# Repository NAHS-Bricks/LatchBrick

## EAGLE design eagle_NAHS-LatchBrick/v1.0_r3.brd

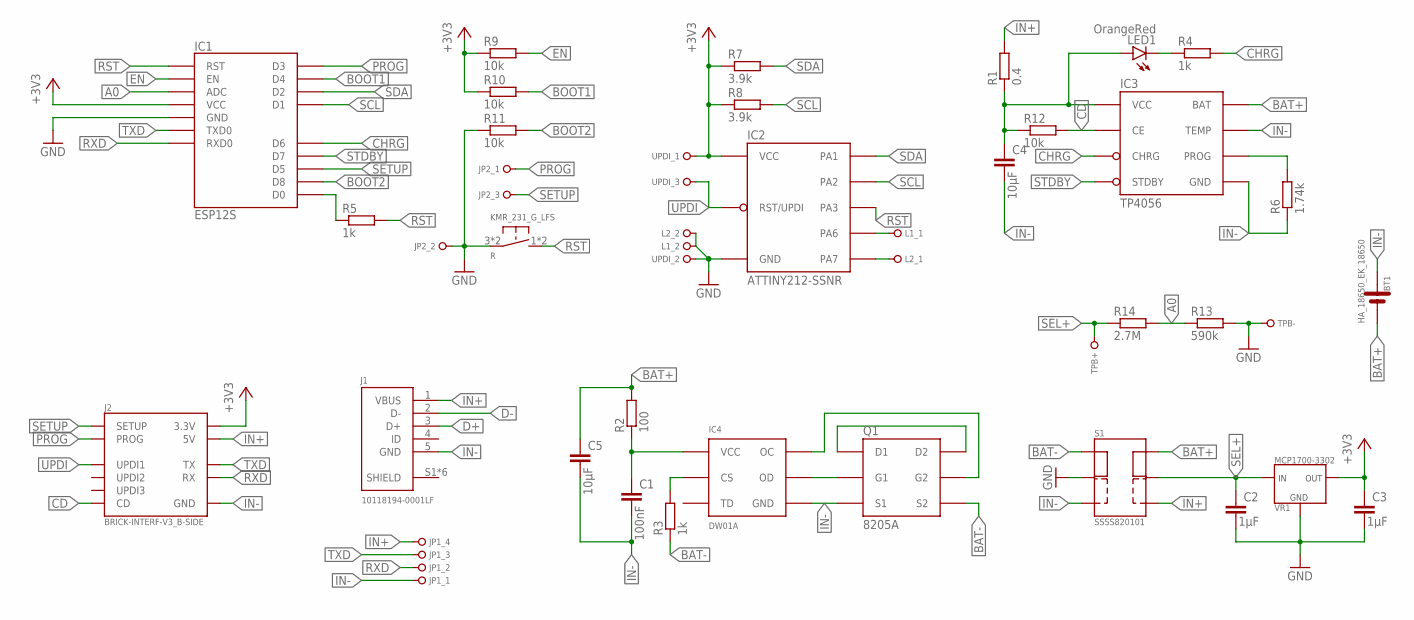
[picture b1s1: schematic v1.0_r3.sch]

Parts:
BT1: HA_18650_EK_18650
C1: 100nF; C0805
C2, C3: 1µF; C0805
C4, C5: 10µF; C0805
IC1: ESP12S
IC2: ATTINY212-SSNR; SOIC8
IC3: TP4056; SO8-THERMALPAD
IC4: DW01A; SOT23-6
J1: 10118194-0001LF
J2: BRICK-INTERF-V3_B-SIDE; DF9-11P-1V(32)
JP1: PINHD_1X04_R_1; 1X04_R_1
JP2: PINHD_1X03_R_1; 1X03_R_1
L1, L2: PINHD_1X02_R_1; 1X02_R_1
LED1: OrangeRed; CHIP-LED0805
Q1: 8205A; TSSOP8
R: KMR_231_G_LFS
R1: 0.4; R0805
R2: 100; R0805
R3, R4, R5: 1k; R0805
R6: 1.74k; R0805
R7, R8: 3.9k; R0805
R9, R10, R11, R12: 10k; R0805
R13: 590k; R0805
R14: 2.7M; R0805
S1: SSSS820101
TPB+: PINHD_1X01_S_0.8; 1X01_S_0.8
TPB-: PINHD_1X01_S_0.8; 1X01_S_0.8
UPDI: PINHD_1X03_R_1; 1X03_R_1
VR1: MCP1700-3302; SOT23

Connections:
+3V3: C3.1, IC1.VCC, IC2.1 (VCC), J2.10 (3.3V), R7.1, R8.1, R9.1, R10.1, UPDI.1, VR1.2 (OUT)
A0: IC1.ADC, R13.1, R14.2
BAT+: BT1.P1 (PLUS), BT1.P2 (PLUS), BT1.P3 (PLUS), C5.1, IC3.5 (BAT), R2.2, S1.6
BAT-: Q1.6 (S2), Q1.7 (S2), R3.1, S1.3
BOOT1: IC1.GPIO2 (D4), R10.2
BOOT2: IC1.GPIO15 (D8), R11.2
CD: IC3.8 (CE), J2.5 (CD), R12.2
CHRG: IC1.GPIO12 (D6), IC3.7 (CHRG), R4.2
D+: J1.3 (D+)
D-: J1.2 (D-)
EN: IC1.EN, R9.2
GND: C2.2, C3.2, IC1.GND, IC2.8 (GND), JP2.2, L1.2, L2.2, R.3 (2), R.4 (2), R11.1, R13.2, S1.2, TPB-.1, UPDI.2, VR1.1 (GND)
IN+: J1.1 (VBUS), J2.4 (5V), JP1.4, R1.2, S1.4
IN-: BT1.M1 (MINUS), BT1.M2 (MINUS), BT1.M3 (MINUS), C1.2, C4.2, C5.2, IC3.1 (TEMP), IC3.3 (GND), IC3.T1 (GND), IC3.T2 (GND), IC3.T3 (GND), IC3.T4 (GND), IC3.T5 (GND), IC3.T6 (GND), IC3.T7 (GND), IC3.T8 (GND), IC4.6 (GND), J1.5 (GND), J2.6 (GND), JP1.1, Q1.2 (S1), Q1.3 (S1), R6.1, S1.1
unnamed: C4.1, IC3.4 (VCC), LED1.A, R1.1, R12.1
unnamed: IC3.2 (PROG), R6.2
unnamed: IC4.2 (CS), R3.2
unnamed: C1.1, IC4.5 (VCC), R2.1
unnamed: IC2.3 (PA7), L2.1
unnamed: IC2.2 (PA6), L1.1
unnamed: LED1.C, R4.1
unnamed: IC4.1 (OD), Q1.4 (G1)
unnamed: Q1.1 (D1), Q1.8 (D2)
unnamed: IC4.3 (OC), Q1.5 (G2)
PROG: IC1.GPIO0 (D3), J2.3 (PROG), JP2.1
RST: IC1.RST, IC2.7 (PA3), R.1, R.2 (1), R5.2
RXD: IC1.RXD0, J2.11 (RX), JP1.2
SCL: IC1.GPIO5 (D1), IC2.5 (PA2), R8.2
SDA: IC1.GPIO4 (D2), IC2.4 (PA1), R7.2
SEL+: C2.1, R14.1, S1.5, TPB+.1, VR1.3 (IN)
SETUP: IC1.GPIO14 (D5), J2.2 (SETUP), JP2.3
SHIELD: J1.S1 (SHIELD), J1.S2 (SHIELD), J1.S3 (SHIELD), J1.S4 (SHIELD), J1.S5 (SHIELD), J1.S6 (SHIELD)
STDBY: IC1.GPIO13 (D7), IC3.6 (STDBY)
TXD: IC1.TXD0, J2.1 (TX), JP1.3
UPDI: IC2.6 (RST/UPDI), J2.7 (UPDI1), UPDI.3
WAKE: IC1.GPIO16 (D0), R5.1

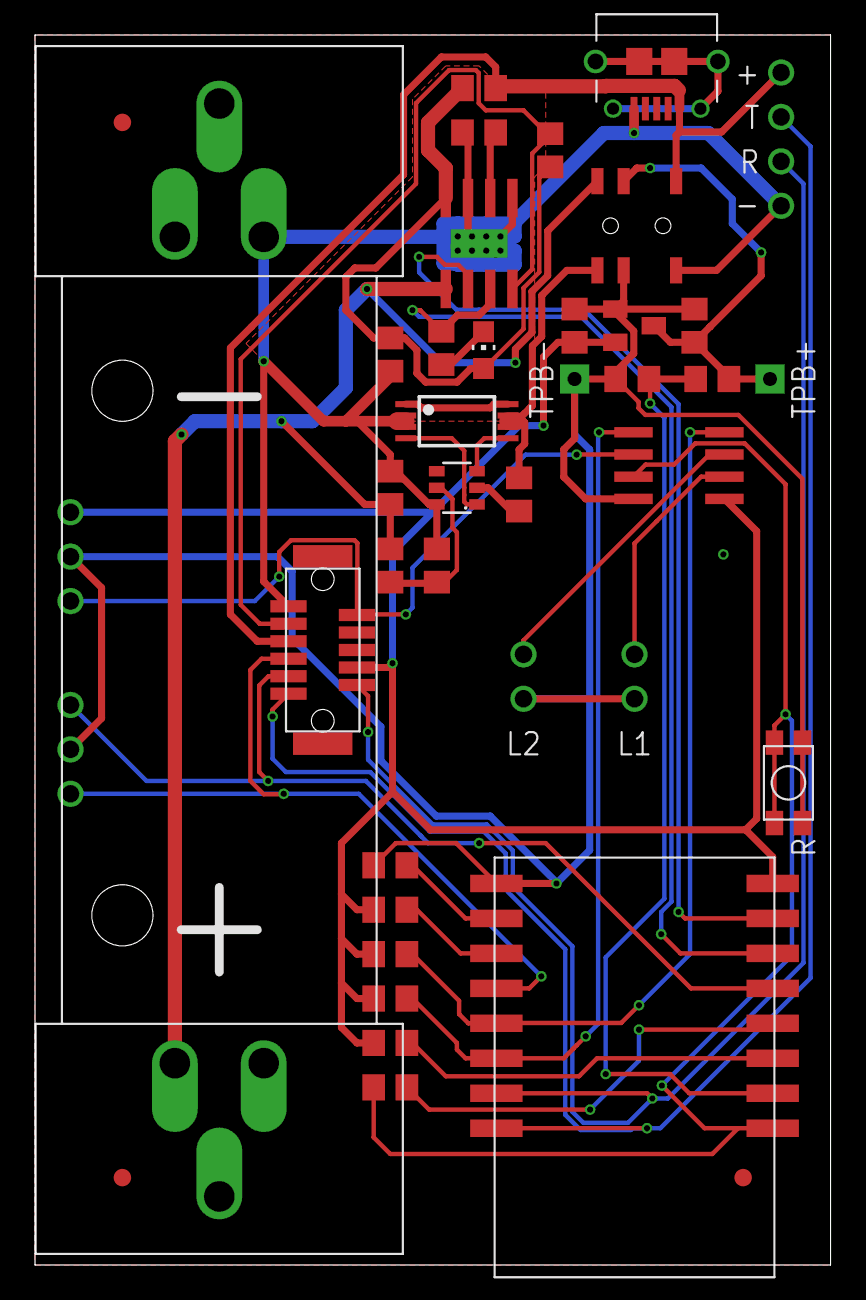
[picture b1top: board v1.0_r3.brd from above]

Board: 2 copper layers, 45.5 x 70.3 mm, 41 parts (0 on the bottom side), 34 nets.

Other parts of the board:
FD1, FD2, FD3: FIDUCIAL

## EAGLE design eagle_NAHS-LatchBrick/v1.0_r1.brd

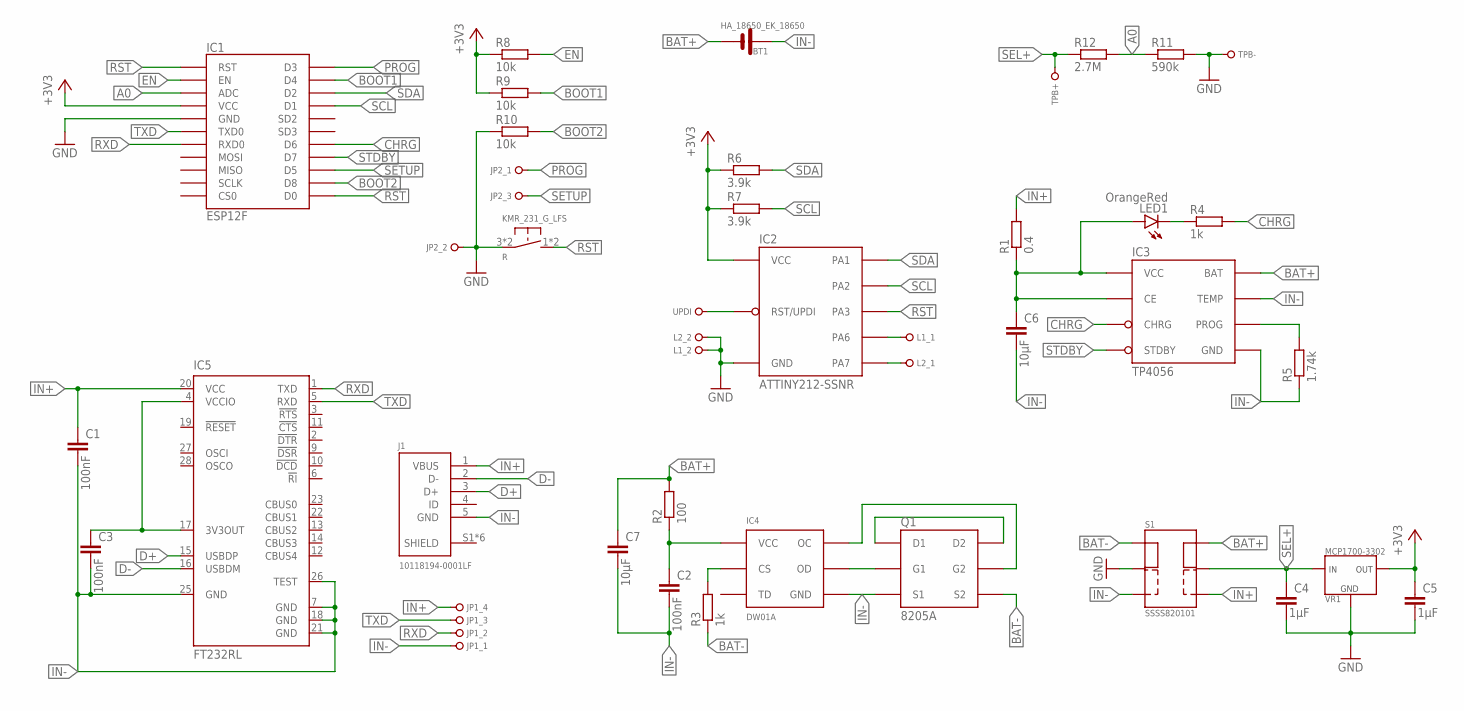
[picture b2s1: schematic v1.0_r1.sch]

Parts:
BT1: HA_18650_EK_18650
C1, C2, C3: 100nF; C0805
C4, C5: 1µF; C0805
C6, C7: 10µF; C0805
IC1: ESP12F; ESP12
IC2: ATTINY212-SSNR; SOIC8
IC3: TP4056; SO8-THERMALPAD
IC4: DW01A; SOT23-6
IC5: FT232RL; SSOP28
J1: 10118194-0001LF
JP1: PINHD_1X04_R_1; 1X04_R_1
JP2: PINHD_1X03_R_1; 1X03_R_1
L1, L2: PINHD_1X02_R_1; 1X02_R_1
LED1: OrangeRed; CHIP-LED0805
Q1: 8205A; TSSOP8
R: KMR_231_G_LFS
R1: 0.4; R0805
R2: 100; R0805
R3, R4: 1k; R0805
R5: 1.74k; R0805
R6, R7: 3.9k; R0805
R8, R9, R10: 10k; R0805
R11: 590k; R0805
R12: 2.7M; R0805
S1: SSSS820101
TPB+: PINHD_1X01_S_0.8; 1X01_S_0.8
TPB-: PINHD_1X01_S_0.8; 1X01_S_0.8
UPDI: PINHD_1X01_S_0.8; 1X01_S_0.8
VR1: MCP1700-3302; SOT23

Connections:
+3V3: C5.1, IC1.VCC, IC2.1 (VCC), R6.1, R7.1, R8.1, R9.1, VR1.2 (OUT)
A0: IC1.ADC, R11.1, R12.2
BAT+: BT1.P1 (PLUS), BT1.P2 (PLUS), BT1.P3 (PLUS), C7.1, IC3.5 (BAT), R2.2, S1.6
BAT-: Q1.6 (S2), Q1.7 (S2), R3.1, S1.3
BOOT1: IC1.GPIO2 (D4), R9.2
BOOT2: IC1.GPIO15 (D8), R10.2
CHRG: IC1.GPIO12 (D6), IC3.7 (CHRG), R4.2
D+: IC5.15 (USBDP), J1.3 (D+)
D-: IC5.16 (USBDM), J1.2 (D-)
EN: IC1.EN, R8.2
GND: C4.2, C5.2, IC1.GND, IC2.8 (GND), JP2.2, L1.2, L2.2, R.3 (2), R.4 (2), R10.1, R11.2, S1.2, TPB-.1, VR1.1 (GND)
IN+: C1.1, IC5.20 (VCC), J1.1 (VBUS), JP1.4, R1.2, S1.4
IN-: BT1.M1 (MINUS), BT1.M2 (MINUS), BT1.M3 (MINUS), C1.2, C2.2, C3.2, C6.2, C7.2, IC3.1 (TEMP), IC3.3 (GND), IC3.T1 (GND), IC3.T2 (GND), IC3.T3 (GND), IC3.T4 (GND), IC3.T5 (GND), IC3.T6 (GND), IC3.T7 (GND), IC3.T8 (GND), IC4.6 (GND), IC5.7 (GND), IC5.18 (GND), IC5.21 (GND), IC5.25 (GND), IC5.26 (TEST), J1.5 (GND), JP1.1, Q1.2 (S1), Q1.3 (S1), R5.1, S1.1
L1: IC2.2 (PA6), L1.1
L2: IC2.3 (PA7), L2.1
unnamed: C6.1, IC3.4 (VCC), IC3.8 (CE), LED1.A, R1.1
unnamed: IC3.2 (PROG), R5.2
unnamed: IC4.2 (CS), R3.2
unnamed: C2.1, IC4.5 (VCC), R2.1
unnamed: LED1.C, R4.1
unnamed: IC4.1 (OD), Q1.4 (G1)
unnamed: Q1.1 (D1), Q1.8 (D2)
unnamed: IC4.3 (OC), Q1.5 (G2)
PROG: IC1.GPIO0 (D3), JP2.1
RST: IC1.GPIO16 (D0), IC1.RST, IC2.7 (PA3), R.1, R.2 (1)
RXD: IC1.RXD0, IC5.1 (TXD), JP1.2
SCL: IC1.GPIO5 (D1), IC2.5 (PA2), R7.2
SDA: IC1.GPIO4 (D2), IC2.4 (PA1), R6.2
SEL+: C4.1, R12.1, S1.5, TPB+.1, VR1.3 (IN)
SETUP: IC1.GPIO14 (D5), JP2.3
SHIELD: J1.S1 (SHIELD), J1.S2 (SHIELD), J1.S3 (SHIELD), J1.S4 (SHIELD), J1.S5 (SHIELD), J1.S6 (SHIELD)
STDBY: IC1.GPIO13 (D7), IC3.6 (STDBY)
TXD: IC1.TXD0, IC5.5 (RXD), JP1.3
UPDI: IC2.6 (RST/UPDI), UPDI.1
VCCIO: C3.1, IC5.4 (VCCIO), IC5.17 (3V3OUT)

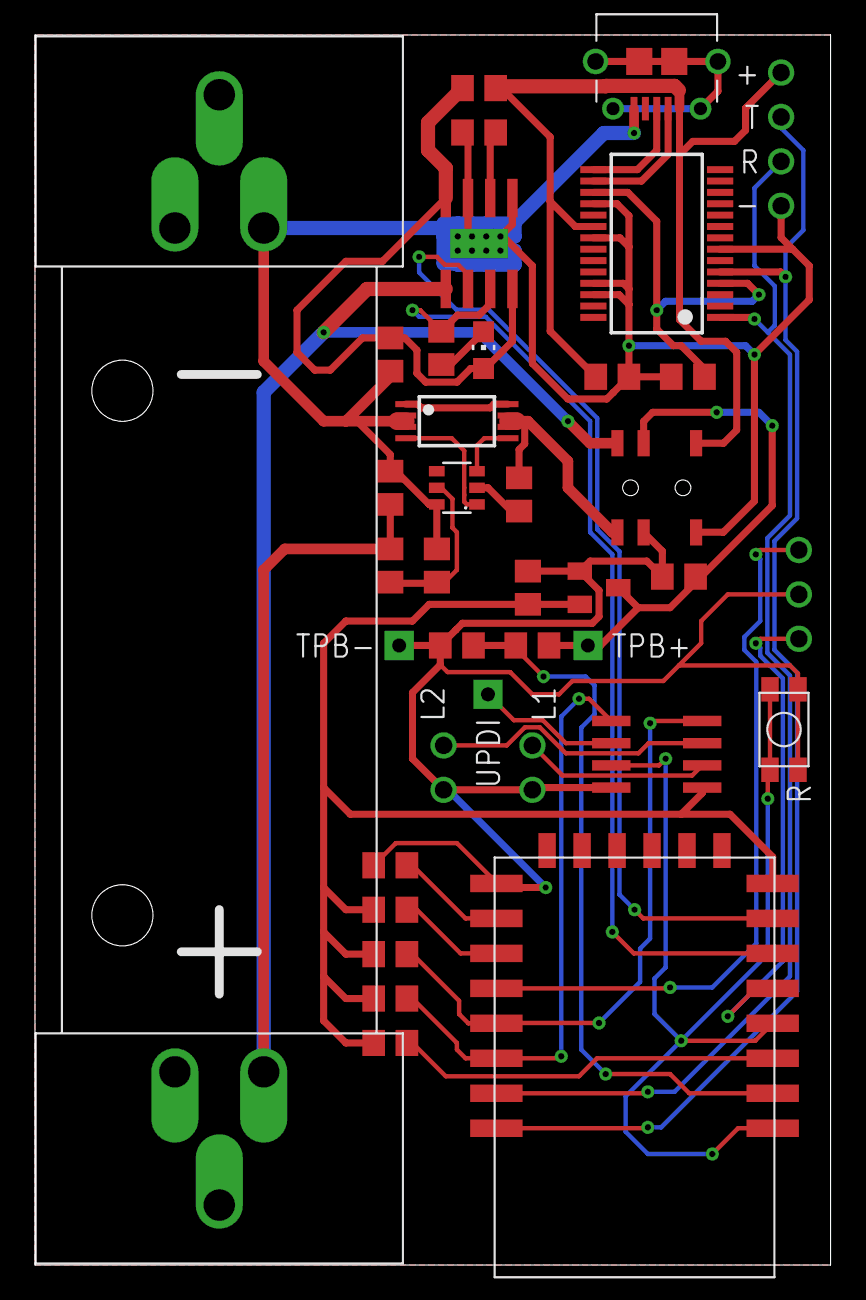
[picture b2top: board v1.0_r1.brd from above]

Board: 2 copper layers, 45.5 x 70.3 mm, 38 parts (0 on the bottom side), 35 nets.

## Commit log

2020-10-21 mit arbeiten an board v1.0_r1 begonnen
2020-10-22 Board v1.0_R1 should allready be finished
2020-10-22 final touches on v1.0_R1 before sending if over to jlcpcb
2020-10-23 started of with programming MainIC and CoIC
2020-11-02 latch interrupts implemented
2020-11-15 implementierung des coic soweit fertig, sollte bereit für test sein
2020-11-17 started interface to coic in arduino
2020-12-30 first round of testing software
2021-01-02 having a twi-prototype working ready to reimplement coic firmware
2021-01-03 zwischenspeichern
2021-01-04 interface working partially, reads seem to be ok, writes have trouble
2021-01-04 i2c interface now working
2021-01-05 latches implemented
2021-01-05 first round of bugfixing
2021-01-06 looks like CoIC is now working as expected
2021-01-12 R2 des boards begonnen und softwaretesting
2021-01-16 saving
2021-01-17 looks like i got the CoIC stable
2021-01-18 komponenten mit kleineren bohrungen eingesetzt
2021-01-19 Finale Version von v1.0_r2, die an JLCPCB übermittelt wurde
2021-01-22 Added INTERRUPT_CTL to CoIC Code
2021-01-23 bugfix in changing interrupt_ctl
2021-02-23 Migration von Arduino zu PlatformIO; mplab prokejt in CoIC Lib verlagert; CoIC wird nun aus Lib verwendet
2021-02-23 BrickSetup testet nun den CoIC
2021-02-27 now using RTCmem lib for RuntimeData
2021-04-28 moved brick-firmware to modular layout
2021-08-10 v1.0 R3 Board done
2022-01-13 build-firmware invoker
2023-01-10 added LICENSE
2023-01-13 v1.0 R4 Board done
2023-11-16 the firmware is now on the latest schema
2024-01-11 v1.0 Board done
